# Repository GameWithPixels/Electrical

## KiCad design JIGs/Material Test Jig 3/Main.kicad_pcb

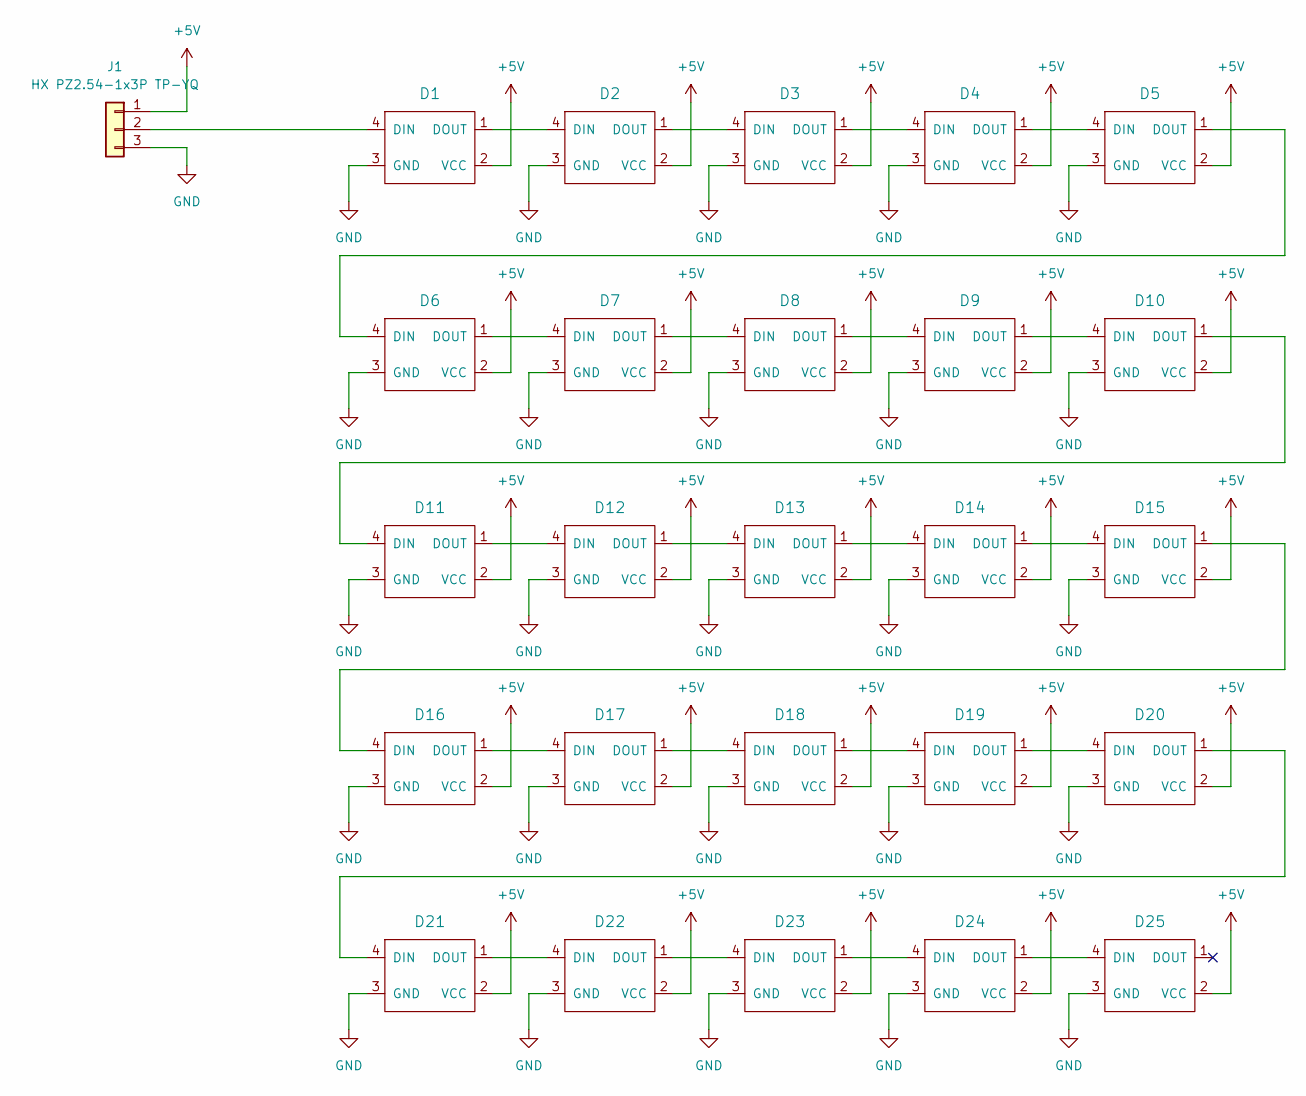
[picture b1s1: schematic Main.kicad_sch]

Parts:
D1, D2, D3, D4, D5, D6, D7, D8, D9, D10, D11, D12, D13, D14, D15, D16, D17, D18, D19, D20, D21, D22, D23, D24, D25: XL-1010RGBC-WS2812B
J1: HX PZ2.54-1x3P TP-YQ; PinHeader_1x03_P2.54mm_Vertical_SMD_Pin1Left

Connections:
+5V: D1.2 (VCC), D2.2 (VCC), D3.2 (VCC), D4.2 (VCC), D5.2 (VCC), D6.2 (VCC), D7.2 (VCC), D8.2 (VCC), D9.2 (VCC), D10.2 (VCC), D11.2 (VCC), D12.2 (VCC), D13.2 (VCC), D14.2 (VCC), D15.2 (VCC), D16.2 (VCC), D17.2 (VCC), D18.2 (VCC), D19.2 (VCC), D20.2 (VCC), D21.2 (VCC), D22.2 (VCC), D23.2 (VCC), D24.2 (VCC), D25.2 (VCC), J1.1
GND: D1.3 (GND), D2.3 (GND), D3.3 (GND), D4.3 (GND), D5.3 (GND), D6.3 (GND), D7.3 (GND), D8.3 (GND), D9.3 (GND), D10.3 (GND), D11.3 (GND), D12.3 (GND), D13.3 (GND), D14.3 (GND), D15.3 (GND), D16.3 (GND), D17.3 (GND), D18.3 (GND), D19.3 (GND), D20.3 (GND), D21.3 (GND), D22.3 (GND), D23.3 (GND), D24.3 (GND), D25.3 (GND), J1.3
unnamed: D1.4 (DIN), J1.2
unnamed: D1.1 (DOUT), D2.4 (DIN)
unnamed: D2.1 (DOUT), D3.4 (DIN)
unnamed: D3.1 (DOUT), D4.4 (DIN)
unnamed: D4.1 (DOUT), D5.4 (DIN)
unnamed: D5.1 (DOUT), D6.4 (DIN)
unnamed: D6.1 (DOUT), D7.4 (DIN)
unnamed: D7.1 (DOUT), D8.4 (DIN)
unnamed: D8.1 (DOUT), D9.4 (DIN)
unnamed: D9.1 (DOUT), D10.4 (DIN)
unnamed: D10.1 (DOUT), D11.4 (DIN)
unnamed: D11.1 (DOUT), D12.4 (DIN)
unnamed: D12.1 (DOUT), D13.4 (DIN)
unnamed: D13.1 (DOUT), D14.4 (DIN)
unnamed: D14.1 (DOUT), D15.4 (DIN)
unnamed: D15.1 (DOUT), D16.4 (DIN)
unnamed: D16.1 (DOUT), D17.4 (DIN)
unnamed: D17.1 (DOUT), D18.4 (DIN)
unnamed: D18.1 (DOUT), D19.4 (DIN)
unnamed: D19.1 (DOUT), D20.4 (DIN)
unnamed: D20.1 (DOUT), D21.4 (DIN)
unnamed: D21.1 (DOUT), D22.4 (DIN)
unnamed: D22.1 (DOUT), D23.4 (DIN)
unnamed: D23.1 (DOUT), D24.4 (DIN)
unnamed: D24.1 (DOUT), D25.4 (DIN)

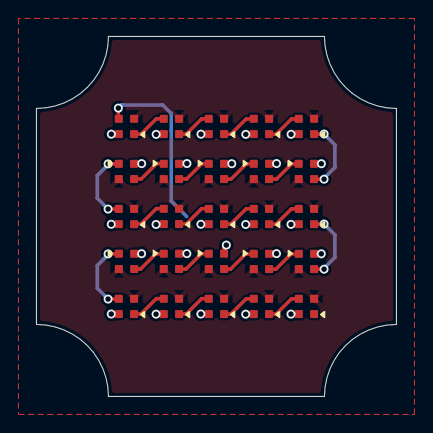
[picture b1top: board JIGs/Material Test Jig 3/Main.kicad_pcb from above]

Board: 4 copper layers, 20.0 x 20.0 mm, 26 parts (1 on the bottom side), 27 nets.

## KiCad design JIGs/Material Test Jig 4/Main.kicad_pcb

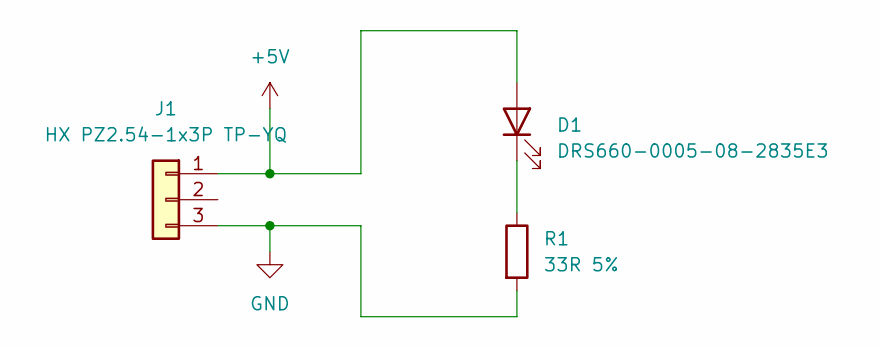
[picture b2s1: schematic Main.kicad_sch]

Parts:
D1: DRS660-0005-08-2835E3
J1: HX PZ2.54-1x3P TP-YQ; PinHeader_1x03_P2.54mm_Vertical_SMD_Pin1Left
R1: 33R 5%; R_0603_1608Metric

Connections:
+5V: D1.2 (A), J1.1
GND: J1.3, R1.2
unnamed: D1.1 (K), R1.1

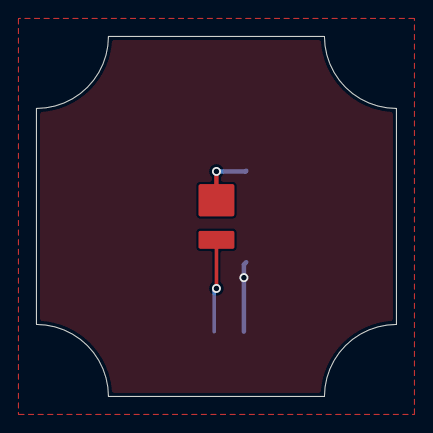
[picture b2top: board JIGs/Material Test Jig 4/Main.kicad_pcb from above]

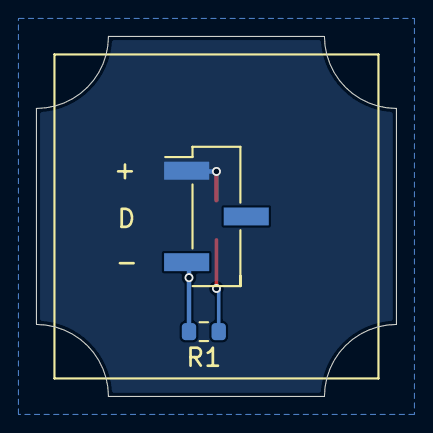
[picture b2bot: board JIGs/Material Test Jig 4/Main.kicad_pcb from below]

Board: 4 copper layers, 20.0 x 20.0 mm, 3 parts (2 on the bottom side), 3 nets.

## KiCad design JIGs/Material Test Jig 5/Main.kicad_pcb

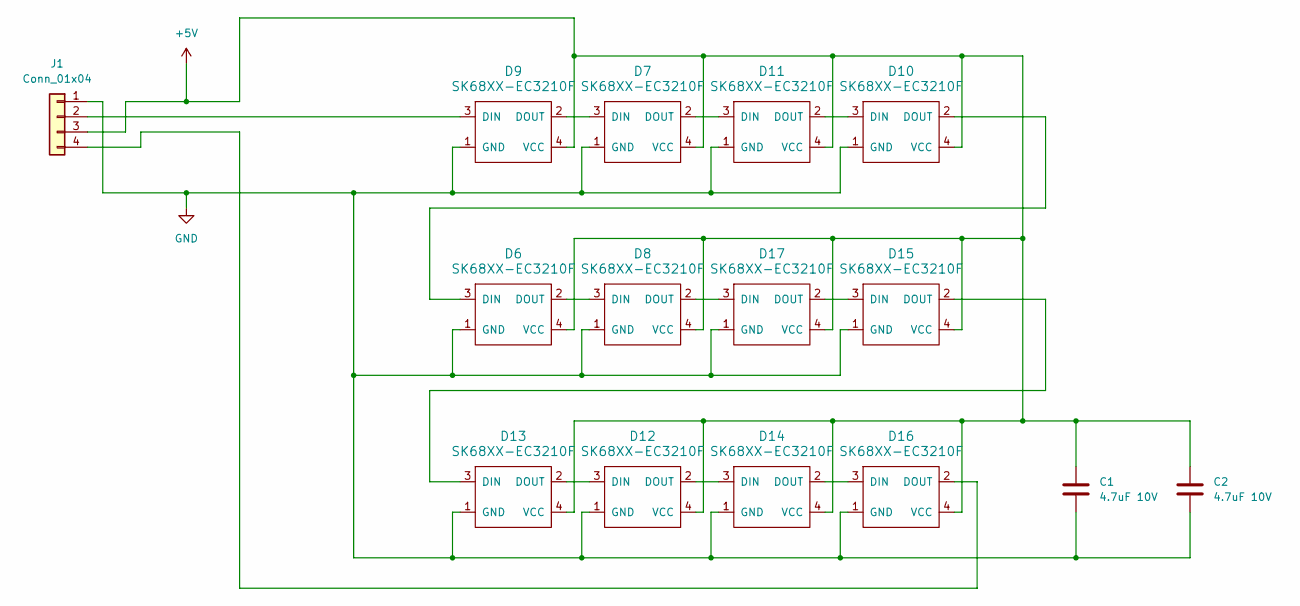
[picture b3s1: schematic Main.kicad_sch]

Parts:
C1, C2: 4.7uF 10V; C_0402_1005Metric
D6, D8, D10, D12, D14, D16: SK68XX-EC3210F
D7, D9, D11, D13, D15, D17: SK68XX-EC3210F; SK68XX-EC3210F-TOPMOUNT
J1: Conn_01x04; Pyre_Con4

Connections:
+5V: C1.1, C2.1, D6.4 (VCC), D7.4 (VCC), D8.4 (VCC), D9.4 (VCC), D10.4 (VCC), D11.4 (VCC), D12.4 (VCC), D13.4 (VCC), D14.4 (VCC), D15.4 (VCC), D16.4 (VCC), D17.4 (VCC), J1.3
GND: C1.2, C2.2, D6.1 (GND), D7.1 (GND), D8.1 (GND), D9.1 (GND), D10.1 (GND), D11.1 (GND), D12.1 (GND), D13.1 (GND), D14.1 (GND), D15.1 (GND), D16.1 (GND), D17.1 (GND), J1.1
unnamed: D6.2 (DOUT), D8.3 (DIN)
unnamed: D7.3 (DIN), D9.2 (DOUT)
unnamed: D9.3 (DIN), J1.2
unnamed: D10.3 (DIN), D11.2 (DOUT)
unnamed: D6.3 (DIN), D10.2 (DOUT)
unnamed: D7.2 (DOUT), D11.3 (DIN)
unnamed: D12.3 (DIN), D13.2 (DOUT)
unnamed: D12.2 (DOUT), D14.3 (DIN)
unnamed: D13.3 (DIN), D15.2 (DOUT)
unnamed: D14.2 (DOUT), D16.3 (DIN)
unnamed: D15.3 (DIN), D17.2 (DOUT)
unnamed: D16.2 (DOUT), J1.4
unnamed: D8.2 (DOUT), D17.3 (DIN)

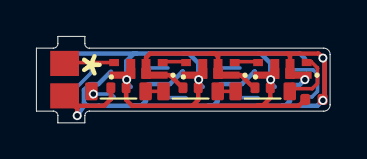
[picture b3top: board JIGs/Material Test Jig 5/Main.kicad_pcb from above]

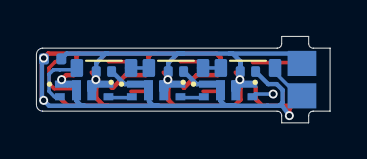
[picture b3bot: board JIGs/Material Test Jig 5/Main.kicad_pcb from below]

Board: 2 copper layers, 16.3 x 4.8 mm, 15 parts (7 on the bottom side), 15 nets.

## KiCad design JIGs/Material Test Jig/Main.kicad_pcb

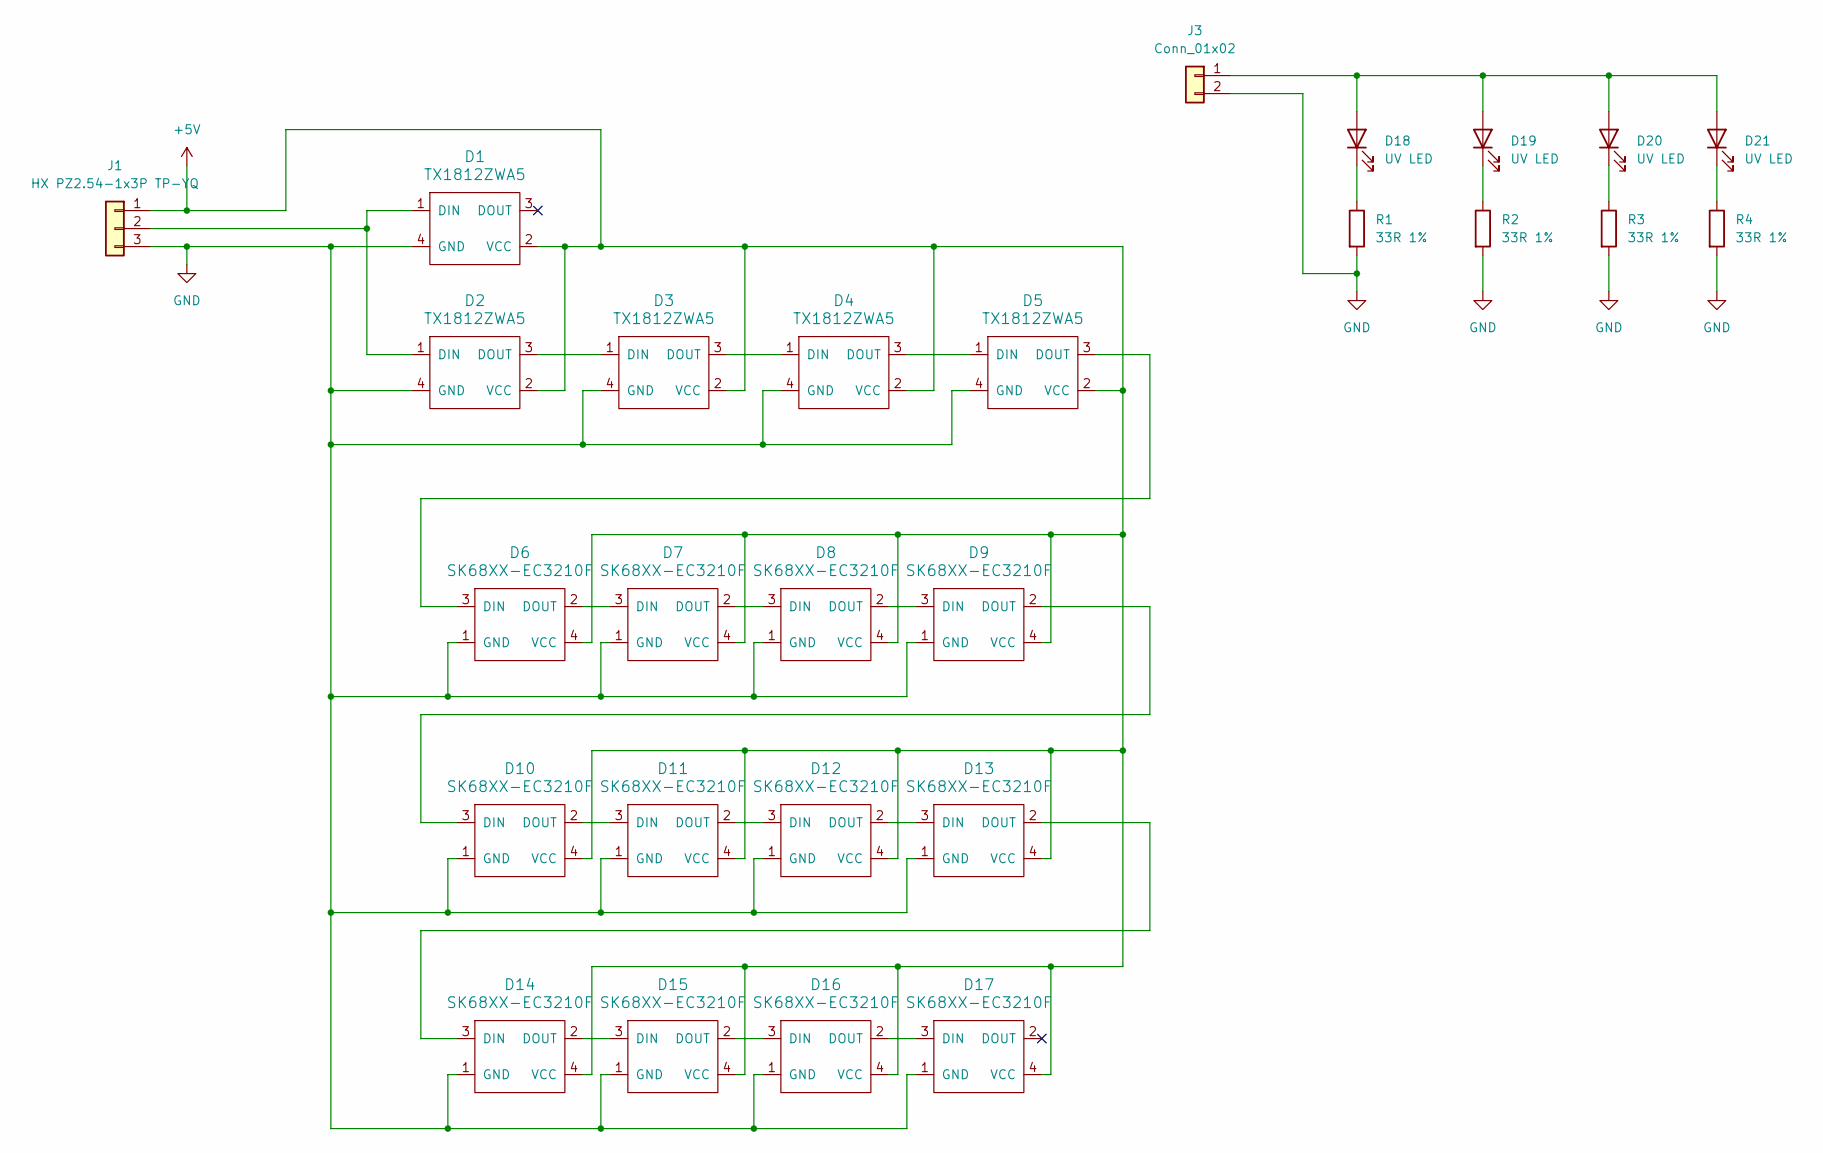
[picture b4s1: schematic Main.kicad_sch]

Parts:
D1, D2, D3, D4, D5: TX1812ZWA5; TX1812Z_2020
D6, D7, D8, D9, D10, D11, D12, D13, D14, D15, D16, D17: SK68XX-EC3210F
D18, D19, D20, D21: UV LED; MHP1016UVACT; Manufacturer Part Number MHP1016UVACT
J1: HX PZ2.54-1x3P TP-YQ; PinHeader_1x03_P2.54mm_Vertical_SMD_Pin1Left
J3: Conn_01x02; PinHeader_1x02_P2.54mm_Vertical
R1, R2, R3, R4: 33R 1%; R_0402_1005Metric; Manufacturer Part Number 0402WGF330JTCE

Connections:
+5V: D1.2 (VCC), D2.2 (VCC), D3.2 (VCC), D4.2 (VCC), D5.2 (VCC), D6.4 (VCC), D7.4 (VCC), D8.4 (VCC), D9.4 (VCC), D10.4 (VCC), D11.4 (VCC), D12.4 (VCC), D13.4 (VCC), D14.4 (VCC), D15.4 (VCC), D16.4 (VCC), D17.4 (VCC), J1.1
GND: D1.4 (GND), D2.4 (GND), D3.4 (GND), D4.4 (GND), D5.4 (GND), D6.1 (GND), D7.1 (GND), D8.1 (GND), D9.1 (GND), D10.1 (GND), D11.1 (GND), D12.1 (GND), D13.1 (GND), D14.1 (GND), D15.1 (GND), D16.1 (GND), D17.1 (GND), J1.3, J3.2, R1.2, R2.2, R3.2, R4.2
unnamed: D1.1 (DIN), D2.1 (DIN), J1.2
unnamed: D2.3 (DOUT), D3.1 (DIN)
unnamed: D3.3 (DOUT), D4.1 (DIN)
unnamed: D4.3 (DOUT), D5.1 (DIN)
unnamed: D5.3 (DOUT), D6.3 (DIN)
unnamed: D6.2 (DOUT), D7.3 (DIN)
unnamed: D7.2 (DOUT), D8.3 (DIN)
unnamed: D8.2 (DOUT), D9.3 (DIN)
unnamed: D9.2 (DOUT), D10.3 (DIN)
unnamed: D10.2 (DOUT), D11.3 (DIN)
unnamed: D11.2 (DOUT), D12.3 (DIN)
unnamed: D12.2 (DOUT), D13.3 (DIN)
unnamed: D13.2 (DOUT), D14.3 (DIN)
unnamed: D14.2 (DOUT), D15.3 (DIN)
unnamed: D15.2 (DOUT), D16.3 (DIN)
unnamed: D16.2 (DOUT), D17.3 (DIN)
unnamed: D18.2 (A), D19.2 (A), D20.2 (A), D21.2 (A), J3.1
unnamed: D18.1 (K), R1.1
unnamed: D19.1 (K), R2.1
unnamed: D20.1 (K), R3.1
unnamed: D21.1 (K), R4.1

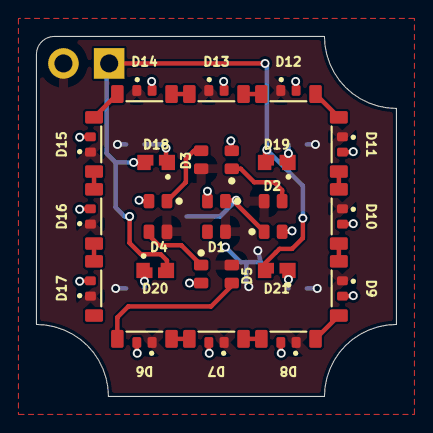
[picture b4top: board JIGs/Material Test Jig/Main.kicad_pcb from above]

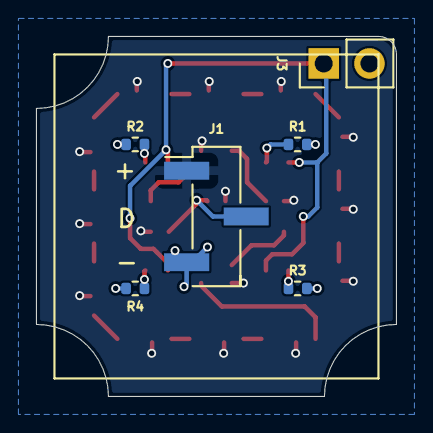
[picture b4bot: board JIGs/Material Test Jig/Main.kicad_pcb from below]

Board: 4 copper layers, 20.0 x 20.0 mm, 27 parts (6 on the bottom side), 23 nets.

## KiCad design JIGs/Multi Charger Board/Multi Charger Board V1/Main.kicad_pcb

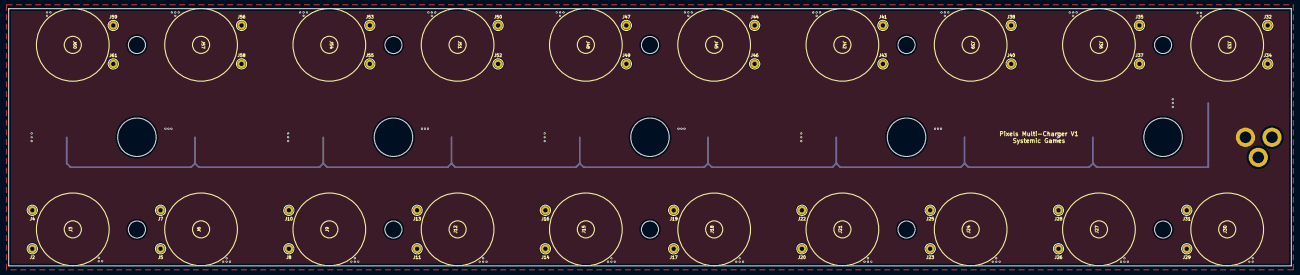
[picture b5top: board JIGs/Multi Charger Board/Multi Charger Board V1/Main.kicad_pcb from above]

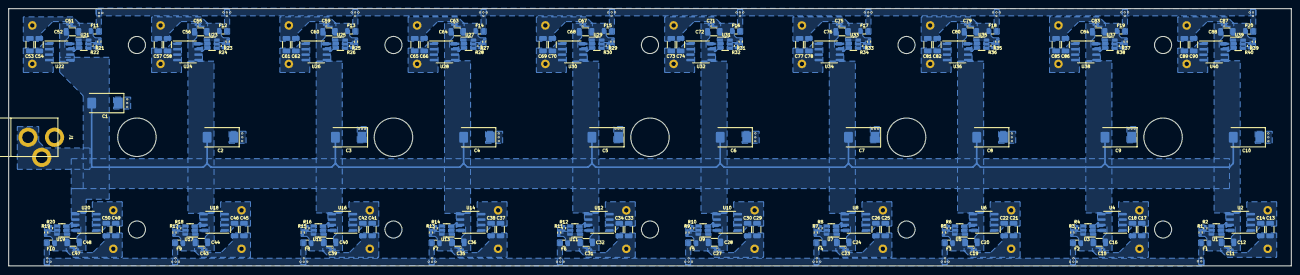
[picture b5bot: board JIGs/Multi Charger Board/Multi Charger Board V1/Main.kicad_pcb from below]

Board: 2 copper layers, 300.0 x 60.2 mm, 251 parts (191 on the bottom side), 102 nets.

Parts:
C1, C2, C3, C4, C5, C6, C7, C8, C9, C10: 220uF 10V; CP_EIA-7343-31_Kemet-D
C11, C15, C19, C23, C27, C31, C35, C39, C43, C47, C51, C55, C59, C63, C67, C71, C75, C79, C83, C87: 0.1uF 10V 20%; C_0402_1005Metric
C12, C16, C20, C24, C28, C32, C36, C40, C44, C48, C52, C56, C60, C64, C68, C72, C76, C80, C84, C88: 47uF 10V 20%; C_1206_3216Metric
C13, C17, C21, C25, C29, C33, C37, C41, C45, C49, C53, C57, C61, C65, C69, C73, C77, C81, C85, C89: 100nF 50V NP0; C_1206_3216Metric
C14, C18, C22, C26, C30, C34, C38, C42, C46, C50, C54, C58, C62, C66, C70, C74, C78, C82, C86, C90: 56nF 50V NP0; C_1206_3216Metric
F1, F2, F3, F4, F5, F6, F7, F8, F9, F10, F11, F12, F13, F14, F15, F16, F17, F18, F19, F20: 500mA ~150mR; Fuse_0805_2012Metric
J1: Barrel_Jack_Switch; BARREL_JACK
J2, J5, J8, J11, J14, J17, J20, J23, J26, J29, J32, J35, J38, J41, J44, J47, J50, J53, J56, J59: Coil B; TestPoint_THTPad_D2.0mm_Drill1.0mm
J3, J6, J9, J12, J15, J18, J21, J24, J27, J30, J33, J36, J39, J42, J45, J48, J51, J54, J57, J60: TX_Coil; TX Coil
J4, J7, J10, J13, J16, J19, J22, J25, J28, J31, J34, J37, J40, J43, J46, J49, J52, J55, J58, J61: Coil A; TestPoint_THTPad_D2.0mm_Drill1.0mm
R1, R3, R5, R7, R9, R11, R13, R15, R17, R19, R21, R23, R25, R27, R29, R31, R33, R35, R37, R39: 200k 1%; R_0402_1005Metric
R2, R4, R6, R8, R10, R12, R14, R16, R18, R20, R22, R24, R26, R28, R30, R32, R34, R36, R38, R40: 84.5k 1%; R_0402_1005Metric
U1, U3, U5, U7, U9, U11, U13, U15, U17, U19, U21, U23, U25, U27, U29, U31, U33, U35, U37, U39: XKT001; SOT-23-6
U2, U4, U6, U8, U10, U12, U14, U16, U18, U20, U22, U24, U26, U28, U30, U32, U34, U36, U38, U40: XKT335; SOIC-8_3.9x4.9mm_P1.27mm

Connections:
+5V: C1.1, C2.1, C3.1, C4.1, C5.1, C6.1, C7.1, C8.1, C9.1, C10.1, F1.1, F2.1, F3.1, F4.1, F5.1, F6.1, F7.1, F8.1, F9.1, F10.1, F11.1, F12.1, F13.1, F14.1, F15.1, F16.1, F17.1, F18.1, F19.1, F20.1, J1.1
GND: C1.2, C2.2, C3.2, C4.2, C5.2, C6.2, C7.2, C8.2, C9.2, C10.2, C11.2, C12.2, C15.2, C16.2, C19.2, C20.2, C23.2, C24.2, C27.2, C28.2, C31.2, C32.2, C35.2, C36.2, C39.2, C40.2, C43.2, C44.2, C47.2, C48.2, C51.2, C52.2, C55.2, C56.2, C59.2, C60.2, C63.2, C64.2, C67.2, C68.2, C71.2, C72.2, C75.2, C76.2, C79.2, C80.2, C83.2, C84.2, C87.2, C88.2, J1.2, J1.3, U1.3 (GND), U2.5 (S), U2.6 (S), U2.7 (S), U3.3 (GND), U4.5 (S), U4.6 (S), U4.7 (S), U5.3 (GND), U6.5 (S), U6.6 (S), U6.7 (S), U7.3 (GND), U8.5 (S), U8.6 (S), U8.7 (S), U9.3 (GND), U10.5 (S), U10.6 (S), U10.7 (S), U11.3 (GND), U12.5 (S), U12.6 (S), U12.7 (S), U13.3 (GND), U14.5 (S), U14.6 (S), U14.7 (S), U15.3 (GND), U16.5 (S), U16.6 (S), U16.7 (S), U17.3 (GND), U18.5 (S), U18.6 (S), U18.7 (S), U19.3 (GND), U20.5 (S), U20.6 (S), U20.7 (S), U21.3 (GND), U22.5 (S), U22.6 (S), U22.7 (S), U23.3 (GND), U24.5 (S), U24.6 (S), U24.7 (S), U25.3 (GND), U26.5 (S), U26.6 (S), U26.7 (S), U27.3 (GND), U28.5 (S), U28.6 (S), U28.7 (S), U29.3 (GND), U30.5 (S), U30.6 (S), U30.7 (S), U31.3 (GND), U32.5 (S), U32.6 (S), U32.7 (S), U33.3 (GND), U34.5 (S), U34.6 (S), U34.7 (S), U35.3 (GND), U36.5 (S), U36.6 (S), U36.7 (S), U37.3 (GND), U38.5 (S), U38.6 (S), U38.7 (S), U39.3 (GND), U40.5 (S), U40.6 (S), U40.7 (S)
unnamed: C11.1, C12.1, C13.2, C14.2, F1.2, J2.1, R1.2, U1.1 (VDD), U1.6 (N/F)
unnamed: C13.1, C14.1, J4.1, U2.1 (D), U2.2 (D), U2.3 (D), U2.4 (D)
unnamed: C15.1, C16.1, C17.2, C18.2, F2.2, J5.1, R3.2, U3.1 (VDD), U3.6 (N/F)
unnamed: C17.1, C18.1, J7.1, U4.1 (D), U4.2 (D), U4.3 (D), U4.4 (D)
unnamed: C19.1, C20.1, C21.2, C22.2, F3.2, J8.1, R5.2, U5.1 (VDD), U5.6 (N/F)
unnamed: C21.1, C22.1, J10.1, U6.1 (D), U6.2 (D), U6.3 (D), U6.4 (D)
unnamed: C23.1, C24.1, C25.2, C26.2, F4.2, J11.1, R7.2, U7.1 (VDD), U7.6 (N/F)
unnamed: C25.1, C26.1, J13.1, U8.1 (D), U8.2 (D), U8.3 (D), U8.4 (D)
unnamed: C27.1, C28.1, C29.2, C30.2, F5.2, J14.1, R9.2, U9.1 (VDD), U9.6 (N/F)
unnamed: C29.1, C30.1, J16.1, U10.1 (D), U10.2 (D), U10.3 (D), U10.4 (D)
unnamed: C31.1, C32.1, C33.2, C34.2, F6.2, J17.1, R11.2, U11.1 (VDD), U11.6 (N/F)
unnamed: C33.1, C34.1, J19.1, U12.1 (D), U12.2 (D), U12.3 (D), U12.4 (D)
unnamed: C35.1, C36.1, C37.2, C38.2, F7.2, J20.1, R13.2, U13.1 (VDD), U13.6 (N/F)
unnamed: C37.1, C38.1, J22.1, U14.1 (D), U14.2 (D), U14.3 (D), U14.4 (D)
unnamed: C39.1, C40.1, C41.2, C42.2, F8.2, J23.1, R15.2, U15.1 (VDD), U15.6 (N/F)
unnamed: C41.1, C42.1, J25.1, U16.1 (D), U16.2 (D), U16.3 (D), U16.4 (D)
unnamed: C43.1, C44.1, C45.2, C46.2, F9.2, J26.1, R17.2, U17.1 (VDD), U17.6 (N/F)
unnamed: C45.1, C46.1, J28.1, U18.1 (D), U18.2 (D), U18.3 (D), U18.4 (D)
unnamed: C47.1, C48.1, C49.2, C50.2, F10.2, J29.1, R19.2, U19.1 (VDD), U19.6 (N/F)
unnamed: C49.1, C50.1, J31.1, U20.1 (D), U20.2 (D), U20.3 (D), U20.4 (D)
unnamed: C51.1, C52.1, C53.2, C54.2, F11.2, J32.1, R21.2, U21.1 (VDD), U21.6 (N/F)
unnamed: C53.1, C54.1, J34.1, U22.1 (D), U22.2 (D), U22.3 (D), U22.4 (D)
unnamed: C55.1, C56.1, C57.2, C58.2, F12.2, J35.1, R23.2, U23.1 (VDD), U23.6 (N/F)
unnamed: C57.1, C58.1, J37.1, U24.1 (D), U24.2 (D), U24.3 (D), U24.4 (D)
unnamed: C59.1, C60.1, C61.2, C62.2, F13.2, J38.1, R25.2, U25.1 (VDD), U25.6 (N/F)
unnamed: C61.1, C62.1, J40.1, U26.1 (D), U26.2 (D), U26.3 (D), U26.4 (D)
unnamed: C63.1, C64.1, C65.2, C66.2, F14.2, J41.1, R27.2, U27.1 (VDD), U27.6 (N/F)
unnamed: C65.1, C66.1, J43.1, U28.1 (D), U28.2 (D), U28.3 (D), U28.4 (D)
unnamed: C67.1, C68.1, C69.2, C70.2, F15.2, J44.1, R29.2, U29.1 (VDD), U29.6 (N/F)
unnamed: C69.1, C70.1, J46.1, U30.1 (D), U30.2 (D), U30.3 (D), U30.4 (D)
unnamed: C71.1, C72.1, C73.2, C74.2, F16.2, J47.1, R31.2, U31.1 (VDD), U31.6 (N/F)
unnamed: C73.1, C74.1, J49.1, U32.1 (D), U32.2 (D), U32.3 (D), U32.4 (D)
unnamed: C75.1, C76.1, C77.2, C78.2, F17.2, J50.1, R33.2, U33.1 (VDD), U33.6 (N/F)
unnamed: C77.1, C78.1, J52.1, U34.1 (D), U34.2 (D), U34.3 (D), U34.4 (D)
unnamed: C79.1, C80.1, C81.2, C82.2, F18.2, J53.1, R35.2, U35.1 (VDD), U35.6 (N/F)
unnamed: C81.1, C82.1, J55.1, U36.1 (D), U36.2 (D), U36.3 (D), U36.4 (D)
unnamed: C83.1, C84.1, C85.2, C86.2, F19.2, J56.1, R37.2, U37.1 (VDD), U37.6 (N/F)
unnamed: C85.1, C86.1, J58.1, U38.1 (D), U38.2 (D), U38.3 (D), U38.4 (D)
unnamed: C87.1, C88.1, C89.2, C90.2, F20.2, J59.1, R39.2, U39.1 (VDD), U39.6 (N/F)
unnamed: C89.1, C90.1, J61.1, U40.1 (D), U40.2 (D), U40.3 (D), U40.4 (D)
unnamed: R1.1, R2.1, U1.4 (R)
unnamed: R2.2, U1.5 (R)
unnamed: R3.1, R4.1, U3.4 (R)
unnamed: R4.2, U3.5 (R)
unnamed: R5.1, R6.1, U5.4 (R)
unnamed: R6.2, U5.5 (R)
unnamed: R7.1, R8.1, U7.4 (R)
unnamed: R8.2, U7.5 (R)
unnamed: R9.1, R10.1, U9.4 (R)
unnamed: R10.2, U9.5 (R)
unnamed: R11.1, R12.1, U11.4 (R)
unnamed: R12.2, U11.5 (R)
unnamed: R13.1, R14.1, U13.4 (R)
unnamed: R14.2, U13.5 (R)
unnamed: R15.1, R16.1, U15.4 (R)
unnamed: R16.2, U15.5 (R)
unnamed: R17.1, R18.1, U17.4 (R)
unnamed: R18.2, U17.5 (R)
unnamed: R19.1, R20.1, U19.4 (R)
unnamed: R20.2, U19.5 (R)
unnamed: R21.1, R22.1, U21.4 (R)
unnamed: R22.2, U21.5 (R)
unnamed: R23.1, R24.1, U23.4 (R)
unnamed: R24.2, U23.5 (R)
unnamed: R25.1, R26.1, U25.4 (R)
unnamed: R26.2, U25.5 (R)
unnamed: R27.1, R28.1, U27.4 (R)
unnamed: R28.2, U27.5 (R)
unnamed: R29.1, R30.1, U29.4 (R)
unnamed: R30.2, U29.5 (R)
unnamed: R31.1, R32.1, U31.4 (R)
unnamed: R32.2, U31.5 (R)
unnamed: R33.1, R34.1, U33.4 (R)
unnamed: R34.2, U33.5 (R)
unnamed: R35.1, R36.1, U35.4 (R)
unnamed: R36.2, U35.5 (R)
unnamed: R37.1, R38.1, U37.4 (R)
unnamed: R38.2, U37.5 (R)
unnamed: R39.1, R40.1, U39.4 (R)
unnamed: R40.2, U39.5 (R)
unnamed: U1.2 (OUT), U2.8 (G)
unnamed: U3.2 (OUT), U4.8 (G)
unnamed: U5.2 (OUT), U6.8 (G)
unnamed: U7.2 (OUT), U8.8 (G)
unnamed: U9.2 (OUT), U10.8 (G)
unnamed: U11.2 (OUT), U12.8 (G)
unnamed: U13.2 (OUT), U14.8 (G)
unnamed: U15.2 (OUT), U16.8 (G)
unnamed: U17.2 (OUT), U18.8 (G)
unnamed: U19.2 (OUT), U20.8 (G)
unnamed: U21.2 (OUT), U22.8 (G)
unnamed: U23.2 (OUT), U24.8 (G)
unnamed: U25.2 (OUT), U26.8 (G)
unnamed: U27.2 (OUT), U28.8 (G)
unnamed: U29.2 (OUT), U30.8 (G)
unnamed: U31.2 (OUT), U32.8 (G)
unnamed: U33.2 (OUT), U34.8 (G)
unnamed: U35.2 (OUT), U36.8 (G)
unnamed: U37.2 (OUT), U38.8 (G)
unnamed: U39.2 (OUT), U40.8 (G)

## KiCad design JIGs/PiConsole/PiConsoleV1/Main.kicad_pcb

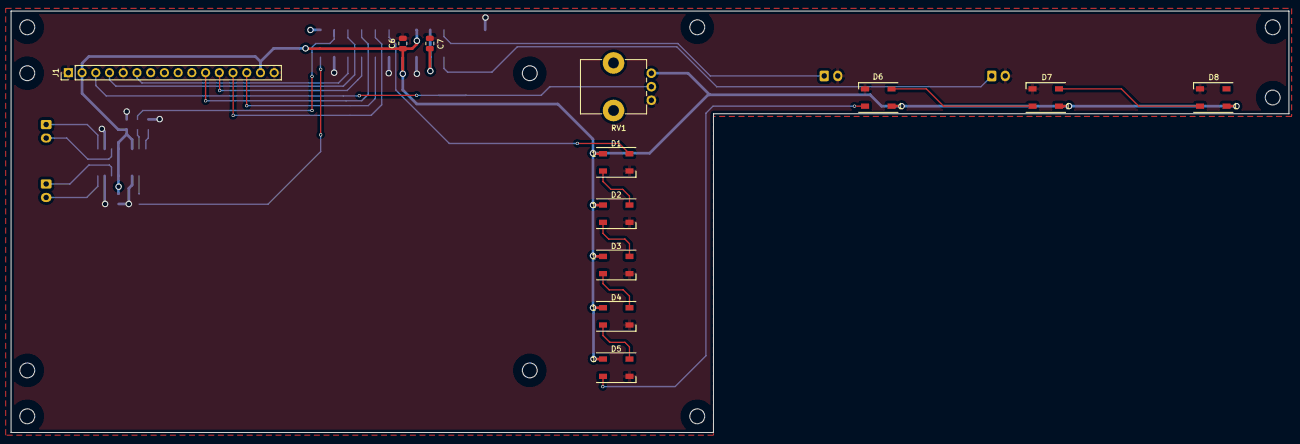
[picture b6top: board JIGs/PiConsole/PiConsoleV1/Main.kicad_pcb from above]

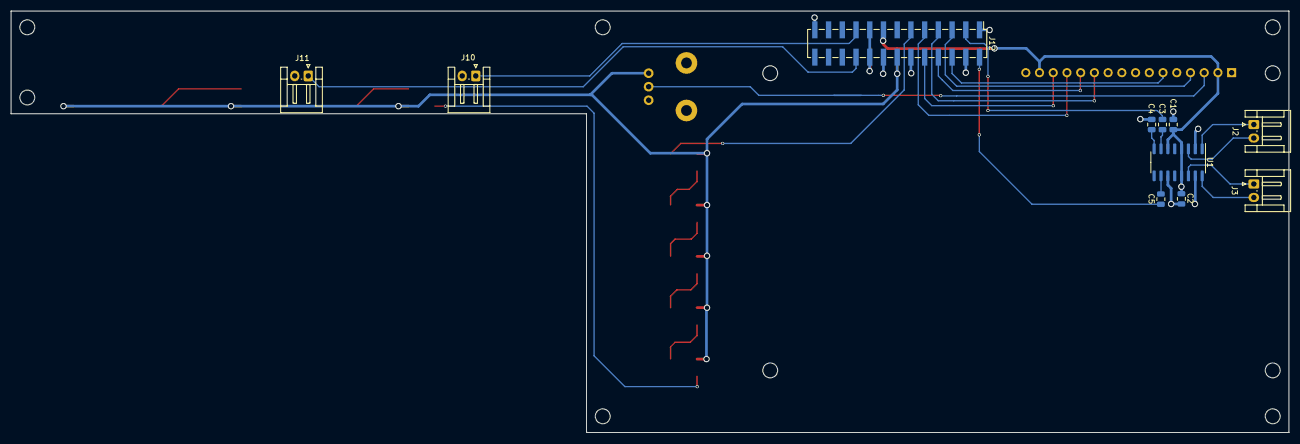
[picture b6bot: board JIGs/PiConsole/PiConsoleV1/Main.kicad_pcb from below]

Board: 2 copper layers, 236.5 x 78.0 mm, 23 parts (11 on the bottom side), 29 nets.

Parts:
C1, C4: 1uF 15V 5%; C_0805_2012Metric
C2, C6, C7: 10uF 15V 5%; C_0805_2012Metric
C3, C5: 0.47uF 15V 5%; C_0805_2012Metric
D1, D2, D3, D4, D5, D6, D7, D8: WS2812B; LED_WS2812B_PLCC4_5.0x5.0mm_P3.2mm
J1: Conn_01x16; PinHeader_1x16_P2.54mm_Vertical
J2, J3, J10, J11: Conn_01x02; JST_EH_S2B-EH_1x02_P2.50mm_Horizontal
J12: Conn_02x13_Top_Bottom; PinHeader_2x13_P2.54mm_Vertical_SMD
RV1: POT 10k; Potentiometer_Alps_RK09K_Single_Vertical
U1: PAM8403; SOP-16_3.9x9.9mm_P1.27mm

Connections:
+3V3: C7.1, J12.17, J12.18
+5V: C1.1, C2.1, C6.1, D1.1, D2.1, D3.1, D4.1, D5.1, D6.1, D7.1, D8.1, J1.2, J1.15, J12.14, J12.15, RV1.1, U1.4, U1.6, U1.13
/CONTRAST: J1.3, RV1.2
AUDIO_L: C3.2, J12.3
AUDIO_R: C5.2, J12.2
GND: C1.2, C2.2, C4.2, C6.2, C7.2, D1.3, D2.3, D3.3, D4.3, D5.3, D6.3, D7.3, D8.3, J1.1, J1.5, J1.16, J10.2, J11.2, J12.4, J12.12, J12.16, J12.25, RV1.3, U1.2, U1.11, U1.15
LCD_BIT4: J1.11, J12.7
LCD_BIT5: J1.12, J12.8
LCD_BIT6: J1.13, J12.9
LCD_BIT7: J1.14, J12.10
LCD_CLOCK: J1.6, J12.6
LCD_RS: J1.4, J12.5
NEO_DATA: D1.4, J12.11
unnamed: C3.1, U1.7
unnamed: C4.1, U1.8
unnamed: C5.1, U1.10
unnamed: D1.2, D2.4
unnamed: D2.2, D3.4
unnamed: D3.2, D4.4
unnamed: D4.2, D5.4
unnamed: D5.2, D6.4
unnamed: D6.2, D7.4
unnamed: D7.2, D8.4
unnamed: J2.1, U1.1
unnamed: J2.2, U1.3
unnamed: J3.1, U1.14
unnamed: J3.2, U1.16
USR_BTN0: J10.1, J12.19
USR_BTN1: J11.1, J12.20
